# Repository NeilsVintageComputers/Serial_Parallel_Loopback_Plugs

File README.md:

# Serial_Parallel_Loopback_Plugs

This board has loopback plugs for Parallel Printer, 9-pin Serial, and 25-pin Serial, they can be cut off into 3 indivdual boards or left as one board with the 3 plugs.
They are wired in common configurations to work with many PC port testing programs.

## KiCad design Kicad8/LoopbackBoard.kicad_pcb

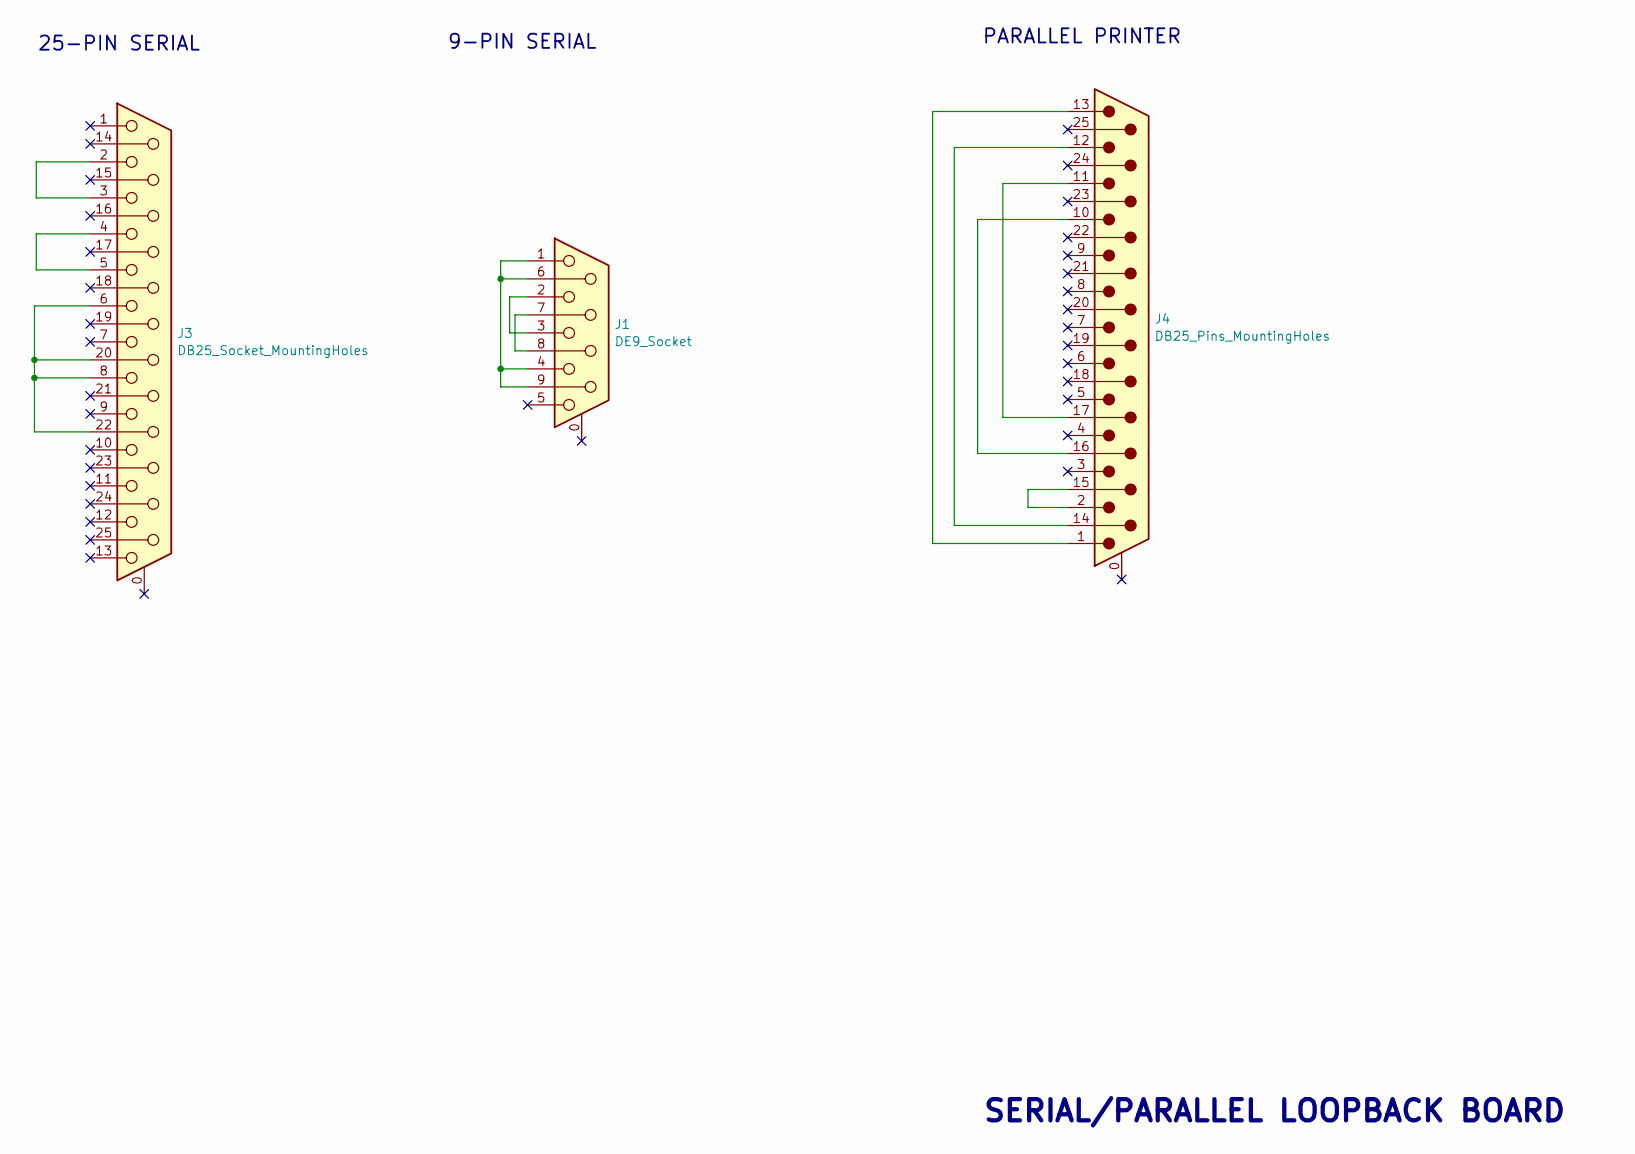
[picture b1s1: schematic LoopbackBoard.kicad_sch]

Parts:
J1: DE9_Socket; Conn_Dsub_DE9F
J3: DB25_Socket_MountingHoles; Conn_Dsub_DB25F
J4: DB25_Pins_MountingHoles; Conn_Dsub_DB25M

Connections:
unnamed: J1.1, J1.4, J1.6, J1.9
unnamed: J1.2, J1.3
unnamed: J1.7, J1.8
unnamed: J3.6, J3.8, J3.20, J3.22
unnamed: J3.2, J3.3
unnamed: J3.4, J3.5
unnamed: J4.12, J4.14
unnamed: J4.2, J4.15
unnamed: J4.10, J4.16
unnamed: J4.11, J4.17
unnamed: J4.1, J4.13

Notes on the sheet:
PARALLEL PRINTER
9-PIN SERIAL
25-PIN SERIAL
SERIAL/PARALLEL LOOPBACK BOARD

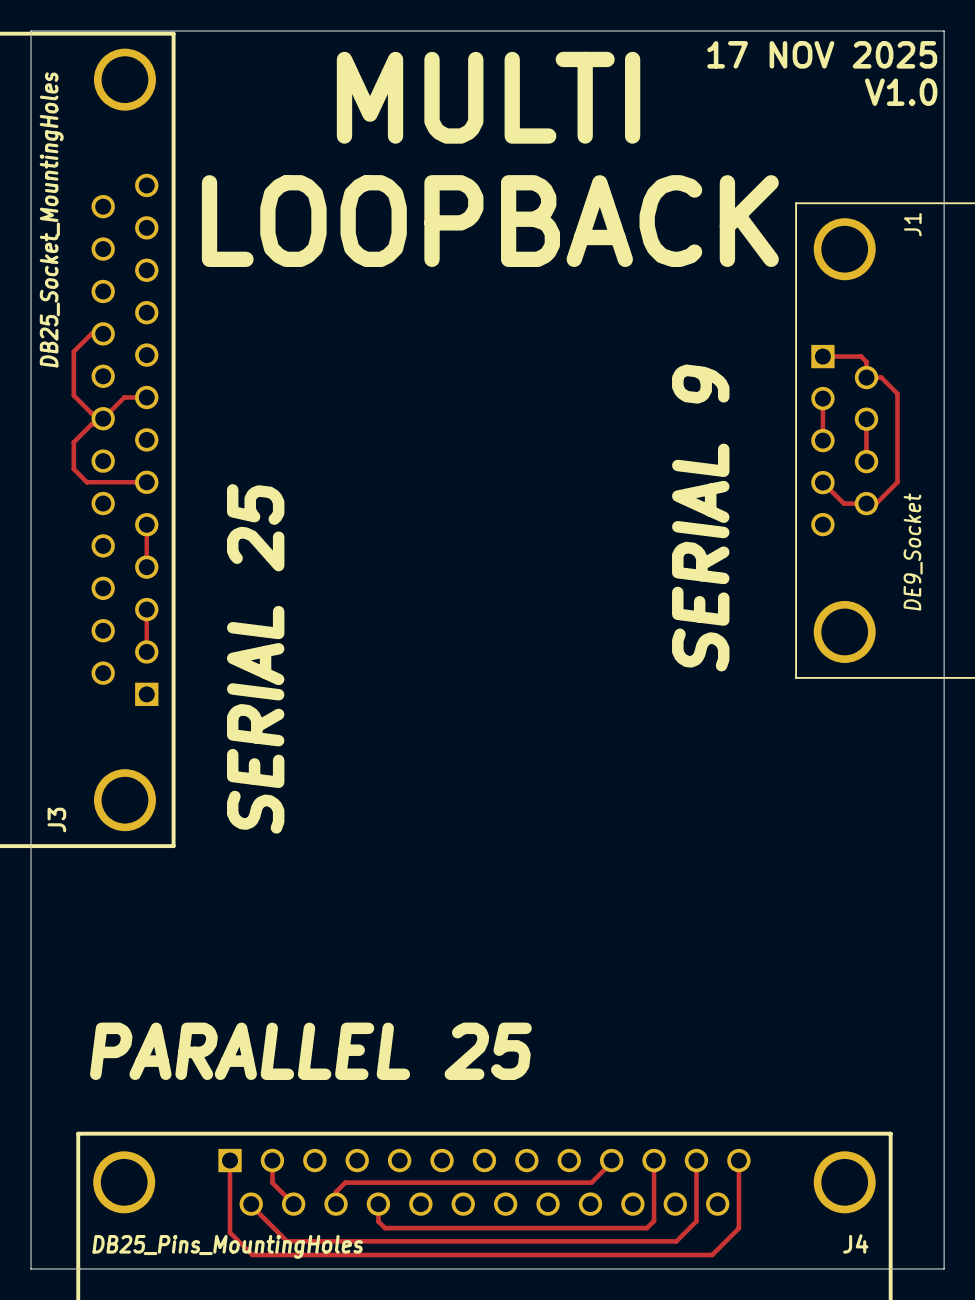
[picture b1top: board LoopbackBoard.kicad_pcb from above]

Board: 2 copper layers, 59.6 x 80.8 mm, 3 parts (0 on the bottom side), 11 nets.
